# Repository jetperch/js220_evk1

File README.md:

# JS220 Evaluation Kit 1

Welcome to the Joulescope JS220 Evaluation Kit 1 (EVK) project.  This EVK
provides a quick and easy way to get started measuring real waveforms with
your Joulescope.  The goal of the EVK is to toggle signals to vary the load.  
Your JS220 will measure this change and display the current waveform in the 
Joulescope UI. 

To get started, connect your JS220 to your host computer.  Install and
start the Joulescope UI.  Select View → Oscilloscope.  

Now plug the EVK into your JS220, like this:

Use the provided USB-C to USB-A cable to connect the EVK to your
host computer.  The Joulescope UI should display an interesting waveform,
like this:

The EVK hardware and firmware are open source and available on 
[GitHub](https://github.com/jetperch/js220_evk1).  View the 
[schematic](https://github.com/jetperch/js220_evk1/blob/main/hardware/js220_evk1.pdf).

The EVK produces this waveform by default.  The EVK is also very flexible.
The EVK runs MicroPython for easy configuration and programming over a
USB-CDC serial port interface.

To get started with MicroPython on your EVK:

1. Connect the EVK to your host computer using the provided USB cable.
2. Install [Thonny](https://thonny.org/)
3. Launch Thonny
4. Select Run → Select interpretter...
   a. Select MicroPython (Raspberry Pi Pico)
   b. Leave port set to <Try to detect port automatically>
   c. OK
5. The "Shell" area at the bottom should display the MicroPython banner ">>>"

You can then run some other tests or create your own.

To stop any load sequence and return to a high impedance load:

    evk.stop()

To power off the supply:

    evk.power_off()

To disable both power and load:

    evk.off()

To run the demo again:

    evk.demo()

To run a simple descending pattern with the buck converter:

    evk.current_range_tester(use_buck=True)

To run a more complicated descending patterh with the buck converter:

    evk.off()
    evk.power_buck(0.6)
    evk.pio_start_sequence(frequency=10_000, sequence='descend')

To provide 1 V from the LDO into a 1 kΩ load:

    evk.off()
    evk.power_ldo(1.0)
    evk.resistance = 1000

To provide 3.3V from the buck converter into a load 1 kΩ || 10 µF:

    evk.off()
    evk.power_ldo(1.0)
    evk.resistance = 1000
    evk.c_10U.on()

To enable both the 1 kΩ and 100 Ω resistors with the 10 µF capacitor:

    evk.stop()
    evk.resistance_on(1000)
    evk.resistance_on(100)
    evk.c_10U.on()

Alternatively:

    evk.stop()
    evk.resistance_mask_on(0x0C)
    evk.c_10U.on()

To disconnect the 10 µF capacitor:
    
    evk.c_10U.off()

To use the PWM capacitor to drive a bipolar current:

    evk.off()
    evk.power_ldo(3.3)
    evk.c_pwm_start(10_000, 0x8000)

To change the LED color to blue:
    
    led.u8(red=0, green=0, blue=255)

You can also animate the LED:

    led.animate_fade([0x00ff00, 0, 0])
    led.animate_rainbow()
    led.stop()

## References:

* [MicroPython](https://micropython.org/)
  * [GitHub](https://github.com/micropython/micropython)
* [Thonny](https://thonny.org/)
* [MicroPython on Raspberry Pi](https://www.raspberrypi.com/documentation/microcontrollers/micropython.html)
  * [Raspberry Pi Pico Python SDK](https://datasheets.raspberrypi.com/pico/raspberry-pi-pico-python-sdk.pdf)
  * [API documentation](https://docs.micropython.org/en/latest/library/rp2.html)
  * [Pico Micropython Examples](https://github.com/raspberrypi/pico-micropython-examples/)
* [Raspberry Pi RP2040 Documentation](https://www.raspberrypi.com/documentation/microcontrollers/rp2040.html)
  * [Pico PIO Examples](https://github.com/raspberrypi/pico-examples/tree/master/pio)
  * [Pico Examples](https://github.com/raspberrypi/pico-examples) for C SDK
    * [Logic Analyzer](https://github.com/raspberrypi/pico-examples/blob/master/pio/logic_analyser/logic_analyser.c) PIO + DMA
    * [PIO](https://github.com/raspberrypi/pico-examples/tree/master/pio)
    * [DMA](https://github.com/raspberrypi/pico-examples/tree/master/dma)
* Controlling the EVK from your host computer
  * [pyboard.py](https://github.com/micropython/micropython/blob/master/tools/pyboard.py)
  * [rshell](https://github.com/dhylands/rshell)
  * [ampy](https://github.com/scientifichackers/ampy)

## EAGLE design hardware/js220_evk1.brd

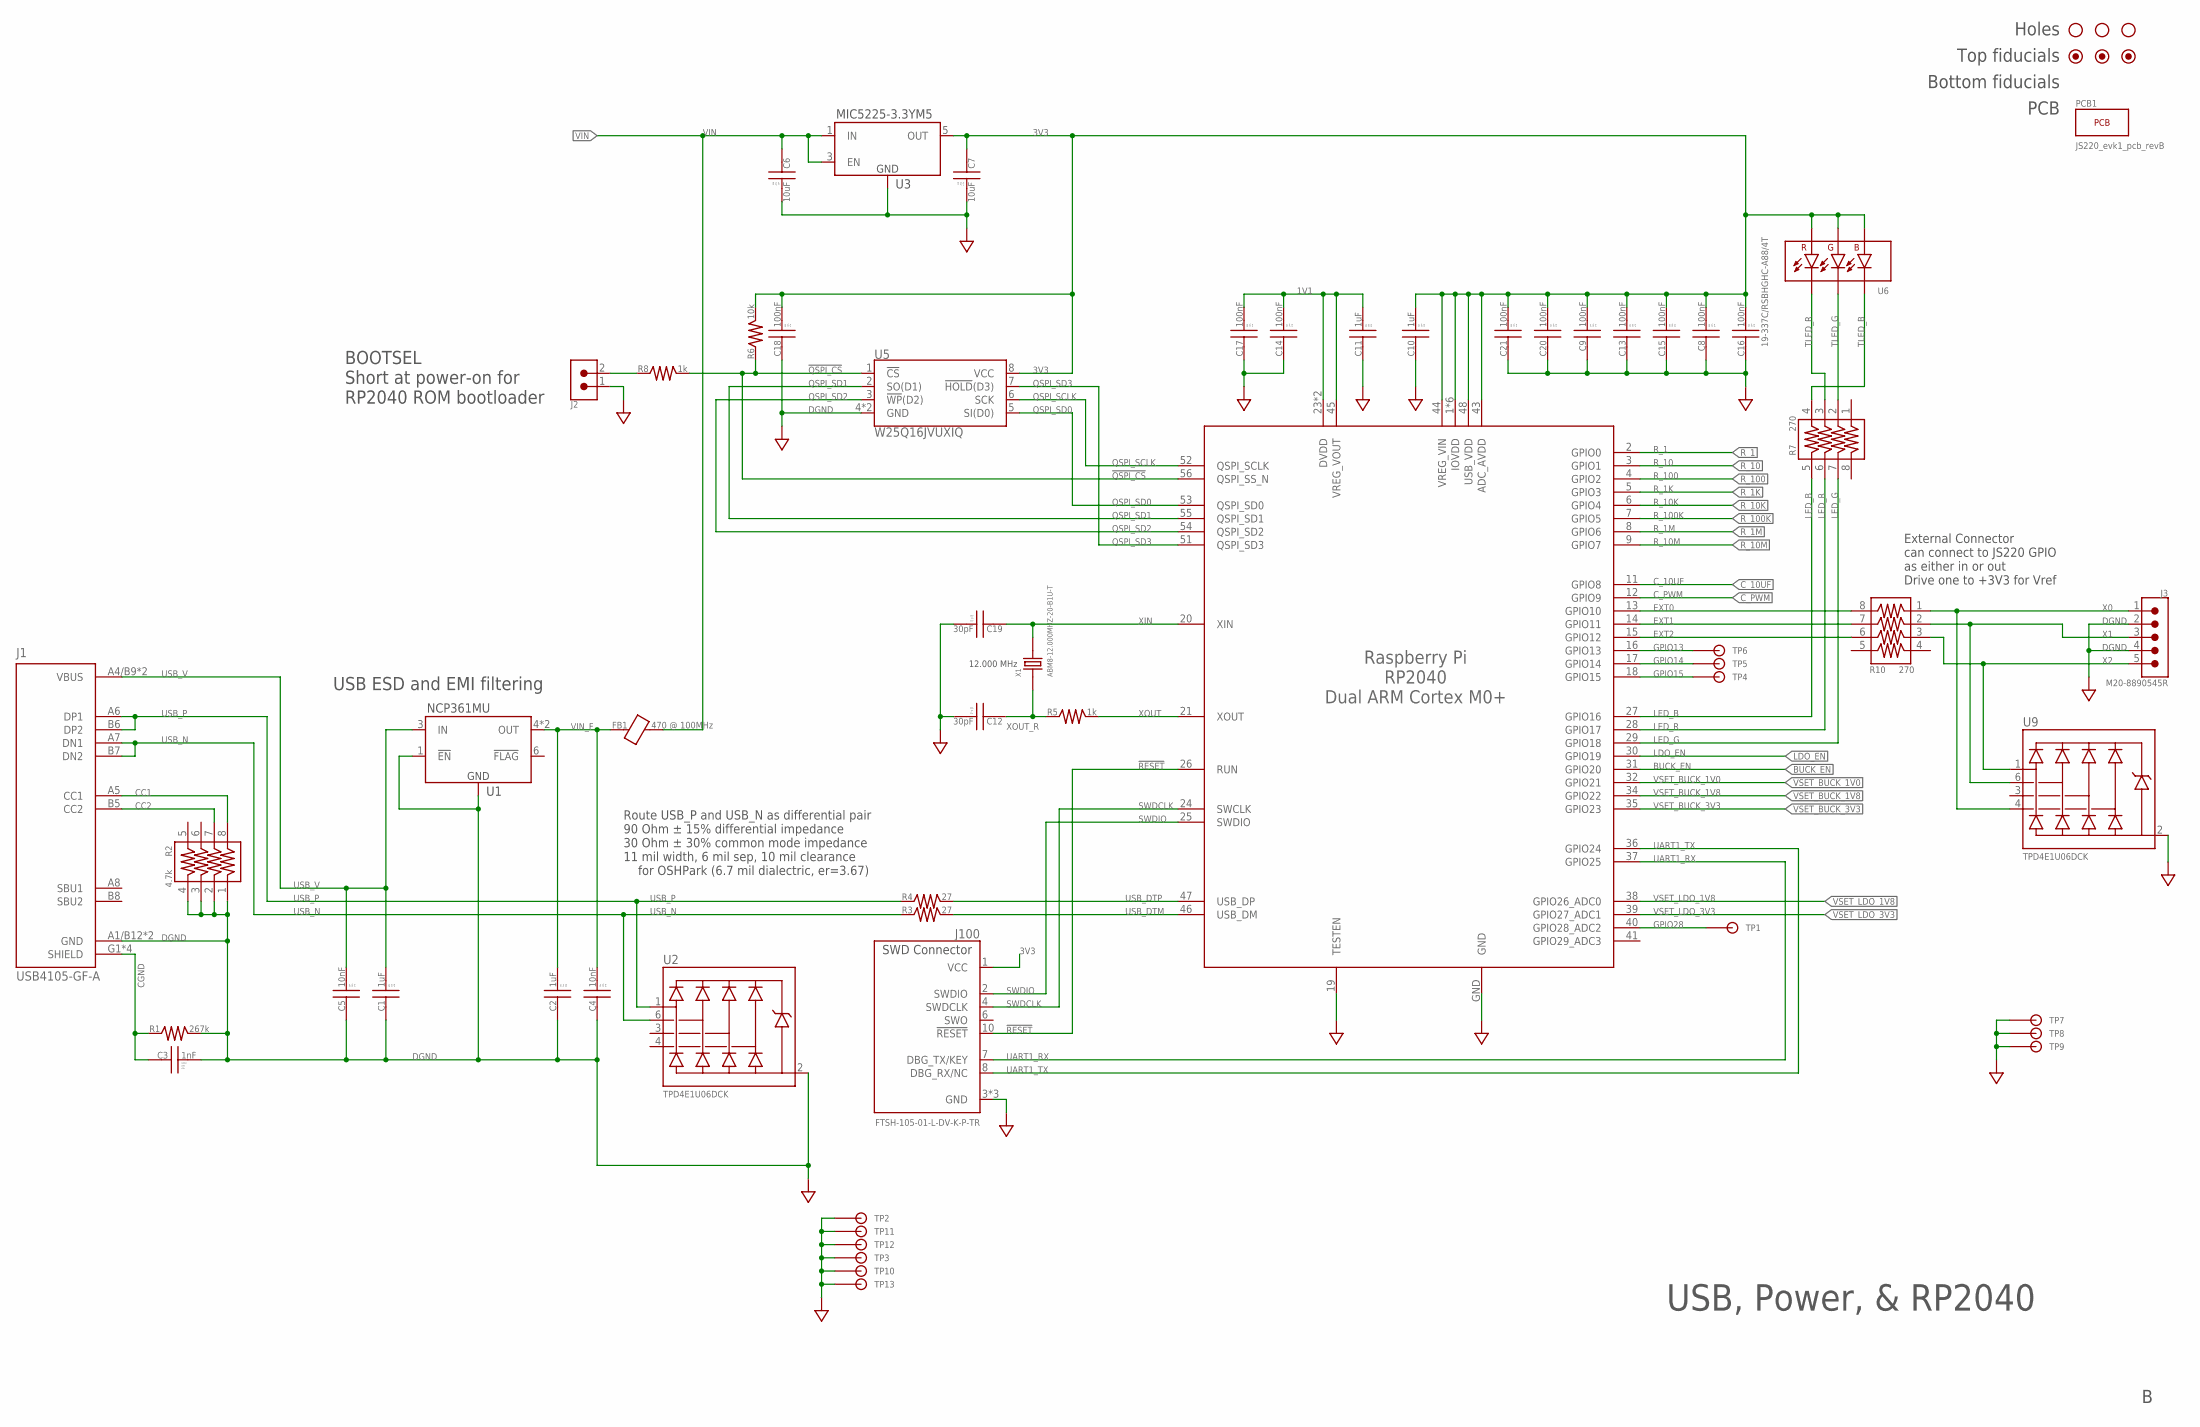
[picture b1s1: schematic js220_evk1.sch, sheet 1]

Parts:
C1, C2, C10, C11: 1uF; 0603; TOLERANCE 20%; VOLTAGE 50V
C3: 1nF; 0805; TOLERANCE 20%; VOLTAGE 1000V
C4, C5: 10nF; 0402; TOLERANCE 10%; VOLTAGE 50V
C6: 10uF; 1206; TOLERANCE 20%; VOLTAGE 10V
C7: 10uF; 0805; TOLERANCE 20%; VOLTAGE 6.3V
C8, C9, C13, C14, C15, C16, C17, C18, C20, C21: 100nF; 0402; TOLERANCE 10%; VOLTAGE 50V
C12, C19: 30pF; 0402; TOLERANCE 5%; VOLTAGE 50V
FB1: 470 @ 100MHz; 0603
FD1, FD2, FD3: DNI; FIDUCIAL_1MM_2MM
H1, H2, H3: STAND-OFFTIGHT; STAND-OFF-TIGHT
J1: USB4105-GF-A; GCT_USB4105_REVA; MPN USB4105-GF-A
J2: CONN_0.1_2X1; CONN_0.1_2X1_M
J3: M20-8890545R; CONN_0.1_5X1_MSR; MPN M20-8890545R
J100: FTSH-105-01-L-DV-K-P-TR; CONN_0.050_5X2_M_SM; MPN FTSH-105-01-L-DV-K-P-TR
R1: 267k; 0402; TOLERANCE 1%
R2: 4.7k; 0402X4; TOLERANCE 5%
R3, R4: 27; 0402; TOLERANCE 1%
R5, R8: 1k; 0402; TOLERANCE 0.1%
R6: 10k; 0402; TOLERANCE 0.1%
R7, R10: 270; 0402X4; TOLERANCE 5%
TP1, TP2, TP3, TP4, TP5, TP6, TP7, TP8, TP9, TP10, TP11, TP12, TP13: TPTP-PTH0.02; TP-PTH0.02
U1: NCP361MU; UDFN-6; MPN NCP361MUTBG
U2, U9: TPD4E1U06DCK; SC-70-6
U3: MIC5225-3.3YM5; SOT23-5; MPN MIC5225-3.3YM5-TR
U4: RP2040; QFN-56G; MPN RP2040
U5: W25Q16JVUXIQ; USON-8_2X3; MPN W25Q16JVUXIQ TR
U6: 19-337C/RSBHGHC-A88/4T; LED_RGB6_1.6X1.6; MPN 19-337C/RSBHGHC-A88/4T
X1: ABM8-12.000MHZ-20-B1U-T; XTAL4_3.2X2.5; MPN ABM8-12.000MHZ-20-B1U-T

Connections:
1V1: C11.2, C14.2, C17.2, U4.23 (DVDD), U4.45 (VREG_VOUT), U4.50 (DVDD)
3V3: C7.1, C8.2, C9.2, C10.2, C13.2, C15.2, C16.2, C18.2, C20.2, C21.2, J100.1 (VCC), R6.2, U3.5 (OUT), U4.1 (IOVDD), U4.10 (IOVDD), U4.22 (IOVDD), U4.33 (IOVDD), U4.42 (IOVDD), U4.43 (ADC_AVDD), U4.44 (VREG_VIN), U4.48 (USB_VDD), U4.49 (IOVDD), U5.8 (VCC), U6.2 (GREEN_ANODE+), U6.4 (RED_ANODE+), U6.6 (BLUE_ANODE+)
!QSPI_CS: R6.1, R8.2, U4.56 (QSPI_SS_N), U5.1 (!CS!)
!RESET: J100.10 (!RESET), U4.26 (RUN)
BUCK_EN: U4.31 (GPIO20); also elsewhere on the board
CC1: J1.A5 (CC1), R2.8 (1B)
CC2: J1.B5 (CC2), R2.7 (2B)
CGND: C3.1, J1.G1 (SHIELD), J1.G2 (SHIELD), J1.G3 (SHIELD), J1.G4 (SHIELD), R1.1
C_10UF: U4.11 (GPIO8); also elsewhere on the board
C_PWM: U4.12 (GPIO9); also elsewhere on the board
DGND: C1.1, C2.1, C3.2, C4.1, C5.1, C6.2, C7.2, C8.1, C9.1, C10.1, C11.1, C12.2, C13.1, C14.1, C15.1, C16.1, C17.1, C18.1, C19.2, C20.1, C21.1, J1.A1/B12 (GND), J1.B1/A12 (GND), J2.1, J3.2, J3.4, J100.3 (GND), J100.5 (GND), J100.9 (GND), R1.2, R2.1 (1A), R2.2 (2A), R2.3 (3A), R2.4 (4A), TP2.1, TP3.1, TP7.1, TP8.1, TP9.1, TP10.1, TP11.1, TP12.1, TP13.1, U1.1 (!EN), U1.2 (GND), U1.GND@PAD (GND), U2.2 (GND), U3.2 (GND), U4.19 (TESTEN), U4.GND, U5.4 (GND), U5.9 (GND), U9.2 (GND); also elsewhere on the board
EXT0: R10.8 (1B), U4.13 (GPIO10)
EXT1: R10.7 (2B), U4.14 (GPIO11)
EXT2: R10.6 (3B), U4.15 (GPIO12)
GPIO13: TP6.1, U4.16 (GPIO13)
GPIO14: TP5.1, U4.17 (GPIO14)
GPIO15: TP4.1, U4.18 (GPIO15)
GPIO28: TP1.1, U4.40 (GPIO28_ADC2)
LDO_EN: U4.30 (GPIO19); also elsewhere on the board
LED_B: R7.5 (4B), U4.27 (GPIO16)
LED_G: R7.7 (2B), U4.29 (GPIO18)
LED_R: R7.6 (3B), U4.28 (GPIO17)
unnamed: J2.2, R8.1
QSPI_SCLK: U4.52 (QSPI_SCLK), U5.6 (SCK)
QSPI_SD0: U4.53 (QSPI_SD0), U5.5 (SI(D0))
QSPI_SD1: U4.55 (QSPI_SD1), U5.2 (SO(D1))
QSPI_SD2: U4.54 (QSPI_SD2), U5.3 (!WP!(D2))
QSPI_SD3: U4.51 (QSPI_SD3), U5.7 (!HOLD!(D3))
R_1: U4.2 (GPIO0); also elsewhere on the board
R_1K: U4.5 (GPIO3); also elsewhere on the board
R_1M: U4.8 (GPIO6); also elsewhere on the board
R_10: U4.3 (GPIO1); also elsewhere on the board
R_10K: U4.6 (GPIO4); also elsewhere on the board
R_10M: U4.9 (GPIO7); also elsewhere on the board
R_100: U4.4 (GPIO2); also elsewhere on the board
R_100K: U4.7 (GPIO5); also elsewhere on the board
SWDCLK: J100.4 (SWDCLK), U4.24 (SWCLK)
SWDIO: J100.2 (SWDIO), U4.25 (SWDIO)
TLED_B: R7.4 (4A), U6.5 (BLUE_CATHODE-)
TLED_G: R7.2 (2A), U6.1 (GREEN_CATHODE-)
TLED_R: R7.3 (3A), U6.3 (RED_CATHODE-)
UART1_RX: J100.7 (DBG_TX/KEY), U4.37 (GPIO25)
UART1_TX: J100.8 (DBG_RX/NC), U4.36 (GPIO24)
USB_DTM: R3.2, U4.46 (USB_DM)
USB_DTP: R4.2, U4.47 (USB_DP)
USB_N: J1.A7 (DN1), J1.B7 (DN2), R3.1, U2.6 (D1-)
USB_P: J1.A6 (DP1), J1.B6 (DP2), R4.1, U2.1 (D1+)
USB_V: C1.2, C5.2, J1.A4/B9 (VBUS), J1.B4/A9 (VBUS), U1.3 (IN)
VIN: C6.1, FB1.2, U3.1 (IN), U3.3 (EN); also elsewhere on the board
VIN_F: C2.2, C4.2, FB1.1, U1.4 (OUT), U1.5 (OUT)
VSET_BUCK_1V0: U4.32 (GPIO21); also elsewhere on the board
VSET_BUCK_1V8: U4.34 (GPIO22); also elsewhere on the board
VSET_BUCK_3V3: U4.35 (GPIO23); also elsewhere on the board
VSET_LDO_1V8: U4.38 (GPIO26_ADC0); also elsewhere on the board
VSET_LDO_3V3: U4.39 (GPIO27_ADC1); also elsewhere on the board
X0: J3.1, R10.1 (1A), U9.4 (D2-)
X1: J3.3, R10.2 (2A), U9.6 (D1-)
X2: J3.5, R10.3 (3A), U9.1 (D1+)
XIN: C19.1, U4.20 (XIN), X1.3 (2)
XOUT: R5.2, U4.21 (XOUT)
XOUT_R: C12.1, R5.1, X1.1

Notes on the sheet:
USB, Power, & RP2040
USB ESD and EMI filtering
Route USB_P and USB_N as differential pair 90 Ohm ± 15% differential impedance 30 Ohm ± 30% common mode impedance 11 mil width, 6 mil sep, 10 mil clearance for OSHPark (6.7 mil dialectric, er=3.67)
12.000 MHz
Holes Top fiducials Bottom fiducials PCB
External Connector can connect to JS220 GPIO as either in or out Drive one to +3V3 for Vref
BOOTSEL Short at power-on for RP2040 ROM bootloader

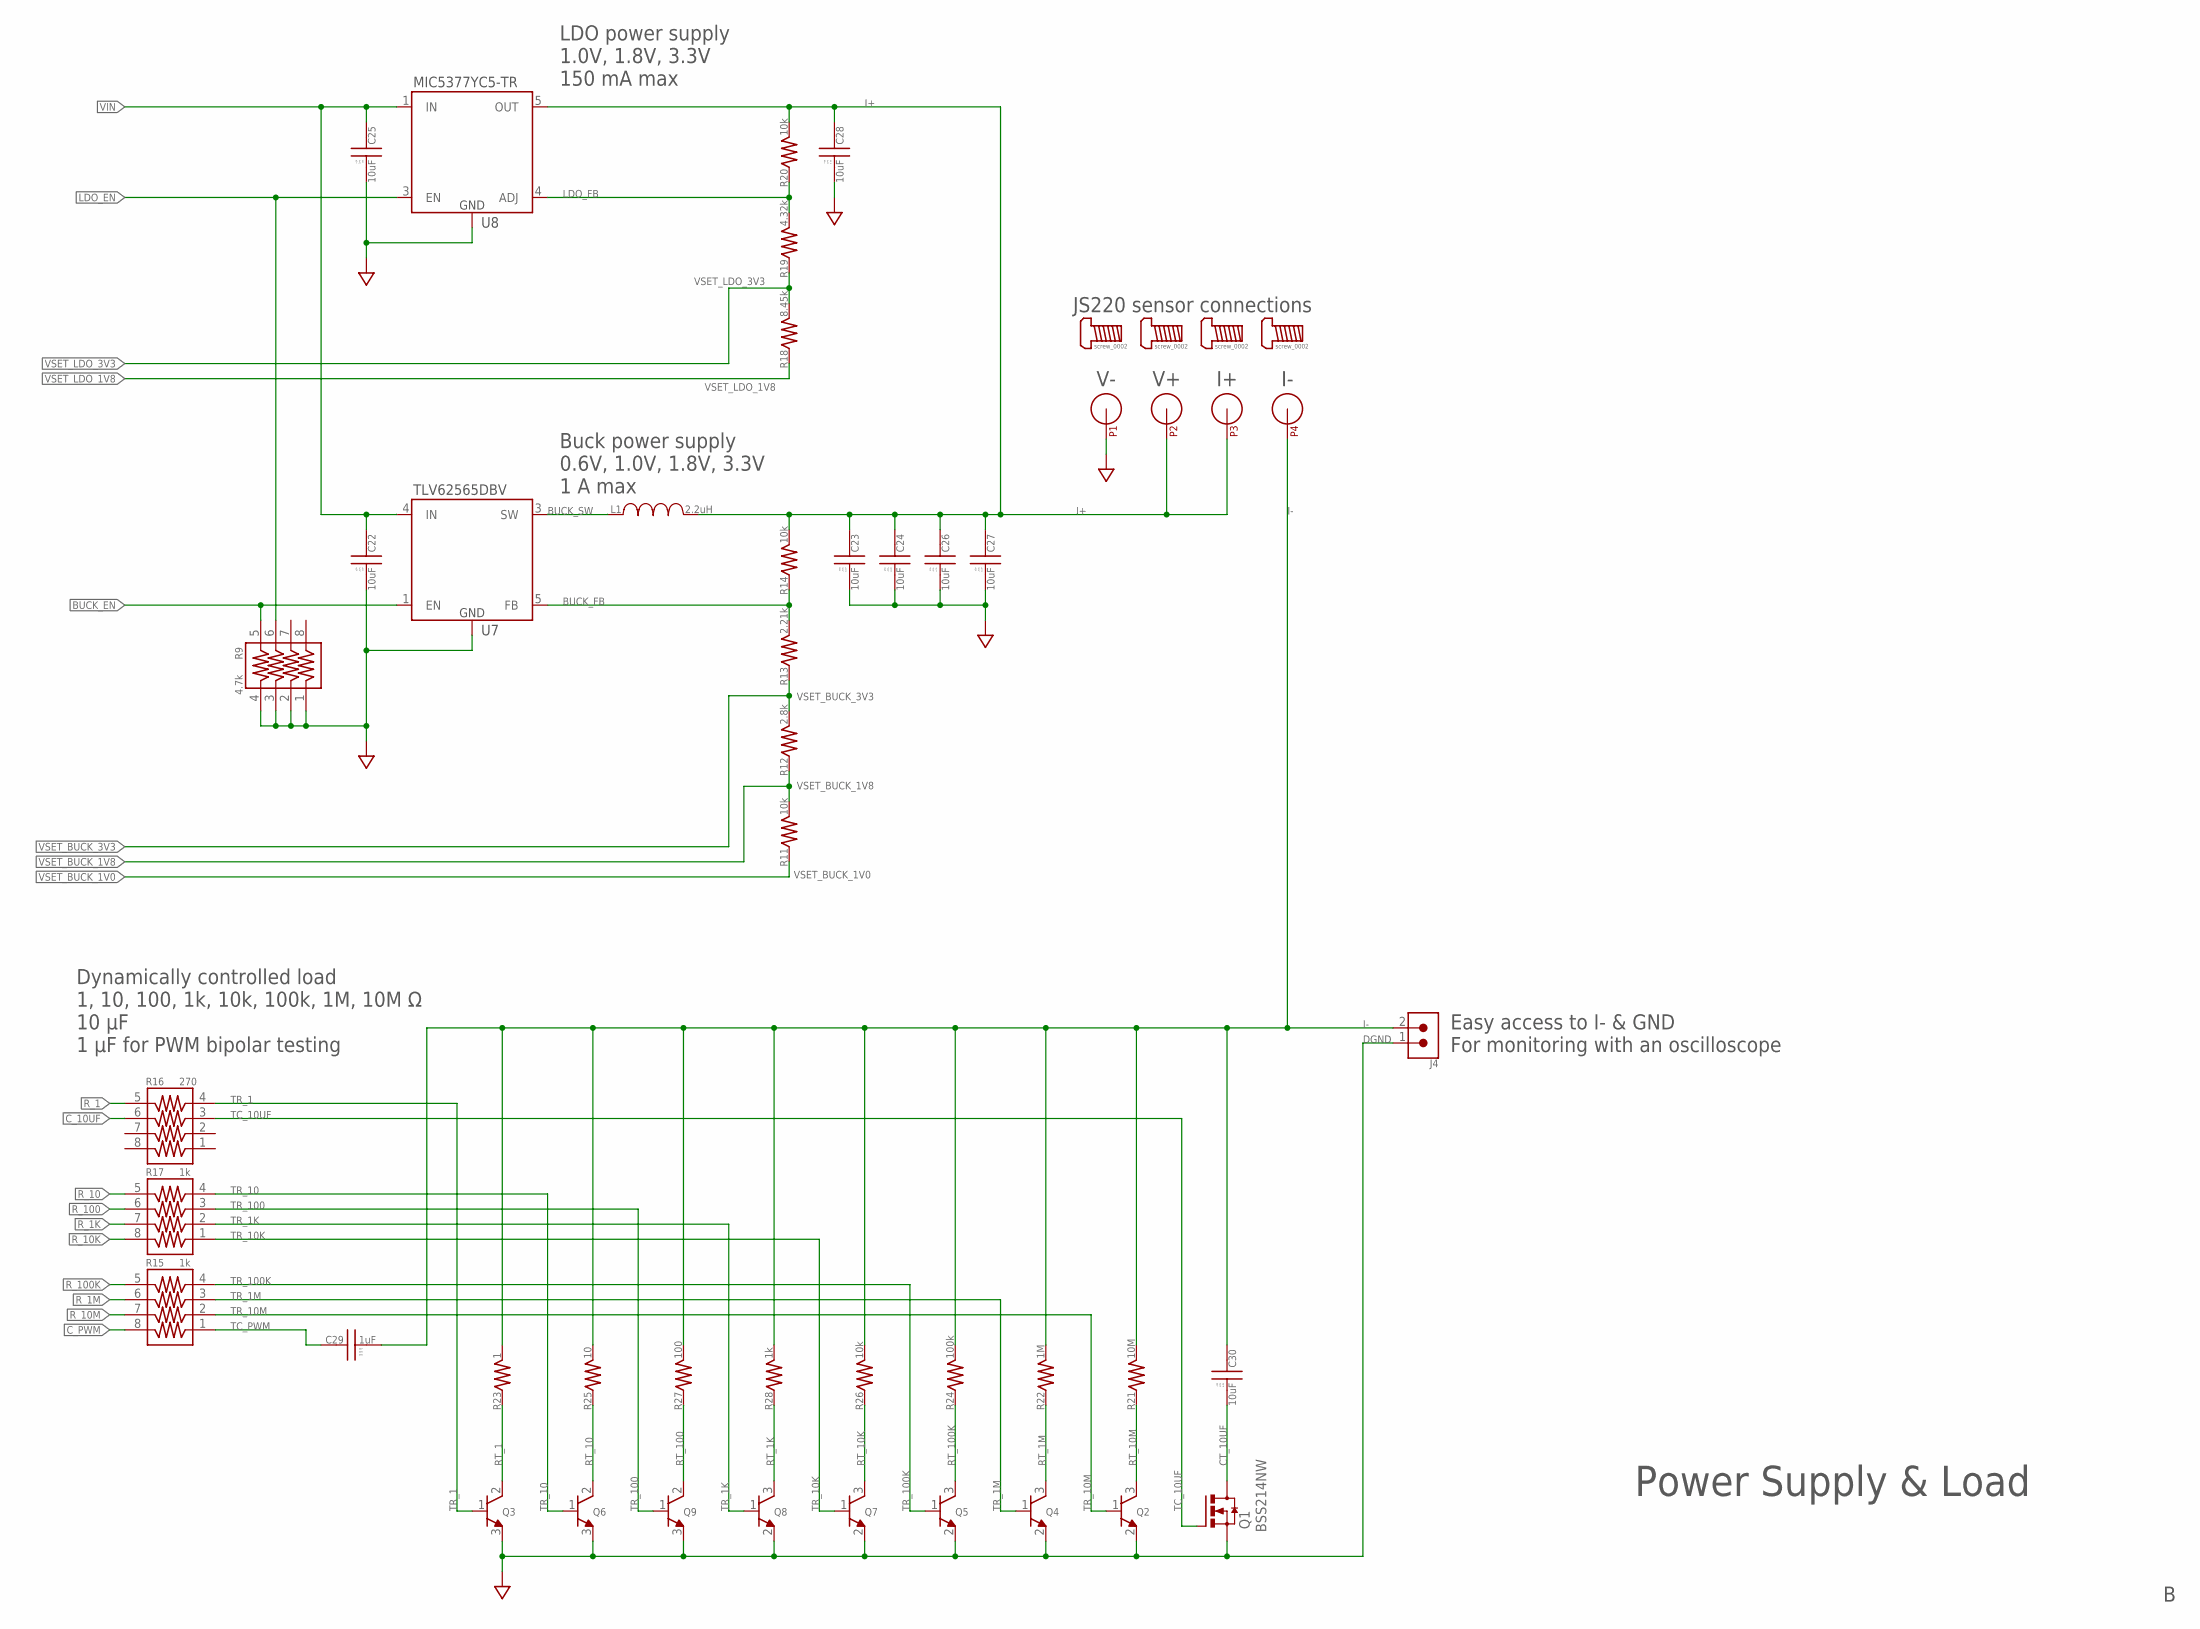
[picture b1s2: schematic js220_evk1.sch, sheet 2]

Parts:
C22, C25: 10uF; 1206; TOLERANCE 20%; VOLTAGE 10V
C23, C24, C26, C27, C28, C30: 10uF; 0805; TOLERANCE 20%; VOLTAGE 6.3V
C29: 1uF; 0603; TOLERANCE 20%; VOLTAGE 50V
J4: CONN_0.1_2X1; CONN_0.1_2X1_M
L1: 2.2uH; LPS4018; MPN NRS4018T2R2MDGJ
P1, P2, P3, P4: P55-271F40N; 72918
Q1: BSS214NW; SOT323-3; MPN BSS214NWH6327XTSA1
Q2, Q4, Q5, Q7, Q8: BC848W; SOT323-3
Q3, Q6, Q9: PBSS4240X; SOT-89; MPN PBSS4240X
R9: 4.7k; 0402X4; TOLERANCE 5%
R11, R14, R20, R26: 10k; 0402; TOLERANCE 0.1%
R12: 2.8k; 0402; TOLERANCE 0.1%
R13: 2.21k; 0402; TOLERANCE 0.1%
R15, R17: 1k; 0402X4; TOLERANCE 5%
R16: 270; 0402X4; TOLERANCE 5%
R18: 8.45k; 0402; TOLERANCE 1%
R19: 4.32k; 0402; TOLERANCE 1%
R21: 10M; 0402; TOLERANCE 1%
R22: 1M; 0402; TOLERANCE 1%
R23: 1; 2512; TOLERANCE 1%
R24: 100k; 0402; TOLERANCE 0.1%
R25: 10; 2512; TOLERANCE 1%
R27: 100; 1206; TOLERANCE 1%
R28: 1k; 0402; TOLERANCE 0.1%
U7: TLV62565DBV; SOT23-5; MPN TLV62565DBV
U8: MIC5377YC5-TR; SC-70-5; MPN MIC5377YC5-TR

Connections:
BUCK_EN: R9.5 (4B), U7.1 (EN); also elsewhere on the board
BUCK_FB: R13.2, R14.1, U7.5 (FB)
BUCK_SW: L1.1, U7.3 (SW)
CT_10UF: C30.2, Q1.3 (D)
C_10UF: R16.6 (3B); also elsewhere on the board
C_PWM: R15.8 (1B); also elsewhere on the board
DGND: C22.2, C23.2, C24.2, C25.2, C26.2, C27.2, C28.2, J4.1, P1.1, Q1.2 (S), Q2.2 (EMITTER), Q3.3 (EMITTER), Q4.2 (EMITTER), Q5.2 (EMITTER), Q6.3 (EMITTER), Q7.2 (EMITTER), Q8.2 (EMITTER), Q9.3 (EMITTER), R9.1 (1A), R9.2 (2A), R9.3 (3A), R9.4 (4A), U7.2 (GND), U8.2 (GND); also elsewhere on the board
I+: C23.1, C24.1, C26.1, C27.1, C28.1, L1.2, P2.1, P3.1, R14.2, R20.2, U8.5 (OUT)
I-: C29.2, C30.1, J4.2, P4.1, R21.2, R22.2, R23.2, R24.2, R25.2, R26.2, R27.2, R28.2
LDO_EN: R9.6 (3B), U8.3 (EN); also elsewhere on the board
LDO_FB: R19.2, R20.1, U8.4 (ADJ)
RT_1: Q3.2 (COLLECTOR), R23.1
RT_1K: Q8.3 (COLLECTOR), R28.1
RT_1M: Q4.3 (COLLECTOR), R22.1
RT_10: Q6.2 (COLLECTOR), R25.1
RT_10K: Q7.3 (COLLECTOR), R26.1
RT_10M: Q2.3 (COLLECTOR), R21.1
RT_100: Q9.2 (COLLECTOR), R27.1
RT_100K: Q5.3 (COLLECTOR), R24.1
R_1: R16.5 (4B); also elsewhere on the board
R_1K: R17.7 (2B); also elsewhere on the board
R_1M: R15.6 (3B); also elsewhere on the board
R_10: R17.5 (4B); also elsewhere on the board
R_10K: R17.8 (1B); also elsewhere on the board
R_10M: R15.7 (2B); also elsewhere on the board
R_100: R17.6 (3B); also elsewhere on the board
R_100K: R15.5 (4B); also elsewhere on the board
TC_10UF: Q1.1 (G), R16.3 (3A)
TC_PWM: C29.1, R15.1 (1A)
TR_1: Q3.1 (BASE), R16.4 (4A)
TR_1K: Q8.1 (BASE), R17.2 (2A)
TR_1M: Q4.1 (BASE), R15.3 (3A)
TR_10: Q6.1 (BASE), R17.4 (4A)
TR_10K: Q7.1 (BASE), R17.1 (1A)
TR_10M: Q2.1 (BASE), R15.2 (2A)
TR_100: Q9.1 (BASE), R17.3 (3A)
TR_100K: Q5.1 (BASE), R15.4 (4A)
VIN: C22.1, C25.1, U7.4 (IN), U8.1 (IN); also elsewhere on the board
VSET_BUCK_1V0: R11.1; also elsewhere on the board
VSET_BUCK_1V8: R11.2, R12.1; also elsewhere on the board
VSET_BUCK_3V3: R12.2, R13.1; also elsewhere on the board
VSET_LDO_1V8: R18.1; also elsewhere on the board
VSET_LDO_3V3: R18.2, R19.1; also elsewhere on the board

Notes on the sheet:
Power Supply & Load
Easy access to I- & GND For monitoring with an oscilloscope
JS220 sensor connections
LDO power supply 1.0V, 1.8V, 3.3V 150 mA max
Buck power supply 0.6V, 1.0V, 1.8V, 3.3V 1 A max
Dynamically controlled load 1, 10, 100, 1k, 10k, 100k, 1M, 10M Ω 10 µF 1 µF for PWM bipolar testing

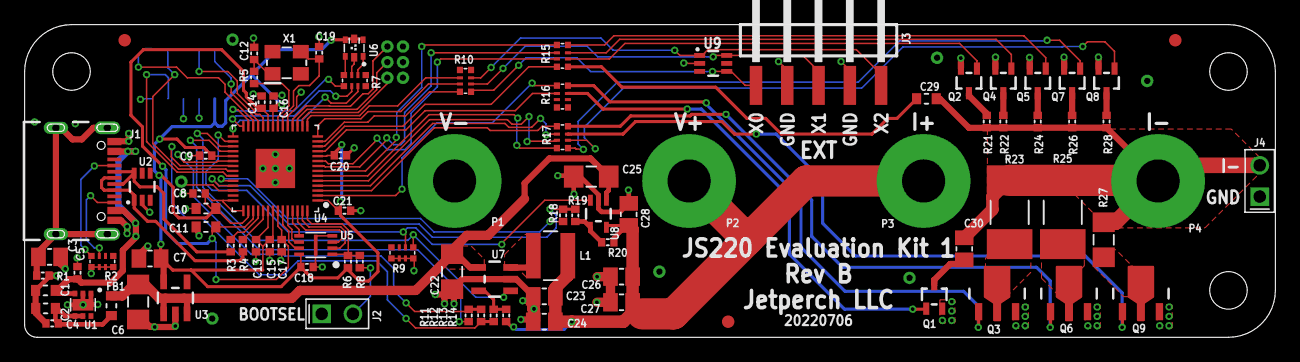
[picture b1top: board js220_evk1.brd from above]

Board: 4 copper layers, 101.6 x 25.4 mm, 109 parts (1 on the bottom side), 85 nets.

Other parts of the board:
DOCFIELD_PCB: DOCFIELD
FRAME_PCB: FRAME_A_L

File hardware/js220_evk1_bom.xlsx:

BOM - All
2022 July 06
# | Qty | Ref Des | Name
1 | 2 | R3, R4 | R0402-27-1%
2 | 3 | R5, R8, R28 | R0402-1k-0.1%
3 | 1 | R13 | R0402-2.21k-0.1%
4 | 1 | R12 | R0402-2.8k-0.1%
5 | 1 | R19 | R0402-4.32k-1%
6 | 1 | R18 | R0402-8.45k-1%
7 | 4 | R11, R14, R20, R26 | R0402-10k-0.1%
8 | 1 | R24 | R0402-100k-0.1%
9 | 1 | R1 | R0402-267k-1%
10 | 1 | R22 | R0402-1M-1%
11 | 1 | R21 | R0402-10M-1%
12 | 1 | R27 | R1206-100-1%
13 | 1 | R23 | R2512-1-1%
14 | 1 | R25 | R2512-10-1%
15 | 3 | R7, R10, R16 | R4_0804-270-5%
16 | 2 | R15, R17 | R4_0804-1k-5%
17 | 2 | R2, R9 | R4_0804-4.7k-5%
18 | 2 | C12, C19 | C0402-30p-C0G-50V-5%
19 | 2 | C4, C5 | C0402-10n-X7R-50V-10%
20 | 10 | C8, C9, C13, C14, C15, C16, C17, C18, C20, C21 | C0402-100n-X7R-50V-10%
21 | 5 | C1, C2, C10, C11, C29 | C0603-1u-X5R-50V-20%
22 | 1 | C3 | C0805-1n-X5R-1000V-20%
23 | 7 | C7, C23, C24, C26, C27, C28, C30 | C0805-10u-X5R-6.3V-20%
24 | 3 | C6, C22, C25 | C1206-10u-X5R-10V-20%
25 | 1 | FB1 | FB0603_470
26 | 1 | L1 | NRS4018T2R2MDGJ
27 | 1 | X1 | ABM8-12.000MHZ-20-B1U-T
28 | 5 | Q2, Q4, Q5, Q7, Q8 | BC848W
29 | 1 | Q1 | BSS214NWH6327XTSA1
30 | 3 | Q3, Q6, Q9 | PBSS4240X
31 | 1 | U6 | 19-337C/RSBHGHC-A88/4T
32 | 1 | U3 | MIC5225-3.3YM5-TR
33 | 1 | U8 | MIC5377YC5-TR
34 | 1 | U1 | NCP361MUTBG
35 | 1 | U4 | RP2040
36 | 1 | U7 | TLV62565DBV
37 | 2 | U2, U9 | TPD4E1U06DCK
38 | 1 | U5 | W25Q16JVUXIQ TR
39 | 1 | J3 | M20-8890545R
40 | 1 | J1 | USB4105-GF-A
41 | 4 | P1, P2, P3, P4 | P55-271F40N
42 | 1 | PCB1 | JS220_evk1_pcb_revB
43 | 4 | U$1, U$2, U$3, U$4 | screw_0002
 | 89

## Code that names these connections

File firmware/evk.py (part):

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
class Pins:
    """Define the pins for the JS220 Evaluation Kit 1."""
    R_1 = 0
    R_10 = 1
    R_100 = 2
    R_1K = 3
    R_10K = 4
    R_100K = 5
    R_1M = 6
    R_10M = 7

    C_10U = 8
    C_PWM = 9
    EXT0 = 10
    EXT1 = 11
    EXT2 = 12

    GPIO13 = 13  # test point
    GPIO14 = 14  # test point
    GPIO15 = 15  # test point

    LED_BLUE = 16
    LED_RED = 17
    LED_GREEN = 18

    LDO_EN = 19
    BUCK_EN = 20

    VSET_BUCK_1V0 = 21
    VSET_BUCK_1V8 = 22
    VSET_BUCK_3V3 = 23

    UART_TX = 24
    UART_RX = 25

    VSET_LDO_1V8 = 26
    VSET_LDO_3V3 = 27
    GPIO28 = 28  # test point
    GPIO29 = 29  # not connected


_R_TO_MASK = {
    1: (1 << Pins.R_1),
    10: (1 << Pins.R_10),
    100: (1 << Pins.R_100),
    1_000: (1 << Pins.R_1K),
    10_000: (1 << Pins.R_10K),
    100_000: (1 << Pins.R_100K),
    1_000_000: (1 << Pins.R_1M),
    10_000_000: (1 << Pins.R_10M),
}


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    def __init__(self):
        self._voltage = 0.0
        self._i_max = 0.0
        self.r_1 = Pin(Pins.R_1, Pin.OUT, value=0)
        self.r_10 = Pin(Pins.R_10, Pin.OUT, value=0)
        self.r_100 = Pin(Pins.R_100, Pin.OUT, value=0)
        self.r_1k = Pin(Pins.R_1K, Pin.OUT, value=0)
        self.r_10k = Pin(Pins.R_10K, Pin.OUT, value=0)
        self.r_100k = Pin(Pins.R_100K, Pin.OUT, value=0)
        self.r_1M = Pin(Pins.R_1M, Pin.OUT, value=0)
        self.r_10M = Pin(Pins.R_10M, Pin.OUT, value=0)
        self.c_10U = Pin(Pins.C_10U, Pin.OUT, value=0)
        self.c_pwm = PWM(Pin(Pins.C_PWM, Pin.OUT, value=0))

        self.ext0 = Pin(Pins.EXT0, Pin.IN, pull=None)
        self.ext1 = Pin(Pins.EXT1, Pin.IN, pull=None)
        self.ext2 = Pin(Pins.EXT2, Pin.IN, pull=None)

        self.ldo_en = Pin(Pins.LDO_EN, Pin.OUT, value=0)
        self.buck_en = Pin(Pins.BUCK_EN, Pin.OUT, value=0)

        self.vset_buck_1v0 = Pin(Pins.VSET_BUCK_1V0, Pin.IN, pull=None)  # drive to 0 to enable
        self.vset_buck_1v8 = Pin(Pins.VSET_BUCK_1V8, Pin.IN, pull=None)  # drive to 0 to enable
        self.vset_buck_3v3 = Pin(Pins.VSET_BUCK_3V3, Pin.IN, pull=None)  # drive to 0 to enable
        self.vset_ldo_1v8 = Pin(Pins.VSET_LDO_1V8, Pin.IN, pull=None)  # drive to 0 to enable
        self.vset_ldo_3v3 = Pin(Pins.VSET_LDO_3V3, Pin.IN, pull=None)  # drive to 0 to enable

        self.led_red = PWM(Pin(Pins.LED_RED))
        self.led_green = PWM(Pin(Pins.LED_GREEN))
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        self.buck_en.off()
        self._voltage = 0.0
        self._i_max = 0.0
        self.vset_buck_1v0.init(Pin.IN, pull=None)
        self.vset_buck_1v8.init(Pin.IN, pull=None)
        self.vset_buck_3v3.init(Pin.IN, pull=None)
        self.vset_ldo_1v8.init(Pin.IN, pull=None)
        self.vset_ldo_3v3.init(Pin.IN, pull=None)

    def power_buck(self, voltage):
        """Configure the buck power supply.
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
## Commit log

2022-09-12 Initial commit.
2022-09-12 Fixed README schematic link.
2022-09-14 Added detail to "Current rating exceeded" error message.
2022-09-16 Added BOM
2022-09-25 Update documents.

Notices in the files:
firmware/evk.py:
Copyright 2022 Jetperch LLC
Licensed under the Apache License, Version 2.0 (the "License");
